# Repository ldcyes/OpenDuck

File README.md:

# OpenDuck 工程

**简体中文** | [English](README_EN.md)

本仓库整理 Microduck 的结构、电气、步态数值验证，以及 RK3576 驱动和训练适配源。**当前是工程仿真预发布，尚未通过实物制造与正常步速行走验收。**

**本次更新：[R29 干涉、线束与质量重算](hardware/r29-resolution/README.md) · [完整 Blender 与证据下载](https://github.com/ldcyes/OpenDuck/releases/tag/r29-r26-closure-candidate-20260929)。**

R29 将嘴部软件行程收至 0–10° 并修正下头壳；指定腿罩/电机配对在四条新质量慢速轨迹中的最低保守名义间隙下界为 11.407 mm。31 根线的防磨件和四工况动力学已补充，但嘴部闭合扭矩仍超过现行 0.05 Nm 结构限制，连续线束及制造公差尚无实物证明，**不能放行行走**。

沿用R25：31根头部导线改为底部接入，保留前盖与原外形比例；收拢活动线束并取消原侧面专用线孔。[底部走线特写](hardware/r25-bottom-head-entry/images/03-bottom-head-entry.png)。仍为工程候选，离散转头检查不代表连续运动或实物验收。

**历史四步回放：[R27：R26整机运动回放](hardware/r27-walk-replay/README.md)。** 使用已保存的195.44秒实际积分轨迹，逐帧驱动完整R26装配并复核覆盖件的刚体干涉增量；R26质量下的动力学和实物行走仍待验收。

**修复前干涉记录：[R28直接区间检查](hardware/r28-r26-interference/README.md)。** 两块新腿罩在四步轨迹的2,345组动态配对中没有新增穿透；最小保守间隙证明仅0.015 mm，制造公差未通过。旧头壳与嘴部在张嘴约8.75°后仍有真实相交。

**2026-09-24设计复核：[腿部比例与电机筛选](docs/proportion-study-20260924/README.md)。前期比较三种方案，现已采用A修改覆盖件；电机和腿长不变，实物步态未验收。**

[R24摄像头前盖](hardware/r24-head-front/README.md)与历史发布继续保留。

[R23合板支架、线束与热连接](hardware/r23-design/README.md)及其[完整工程](https://github.com/ldcyes/OpenDuck/releases/tag/r23-integrated-power-design-20260922)继续保留。

| 范围 | 早期基线（R23补充见上方入口） | 已有结果与边界 |
|---|---|---|
| 结构与装配 | R20 / R13.7 | 557件，名义质量4.195094 kg；72对参考窄/未证、34对实际名义接口仍保留 |
| 运动 | R21 / R13.8 | 实际身体侧倾与上头壳固定点横摆均减少约28.6%；慢速四步195.44 s；四种数值工况通过，原40%/30%目标未达到 |
| 电气 | R13原生板图 | 12种、13块；原规则DRC为0；额外启用忽略规则仍有43项警告；6块PCB、U2D2及相机待详细安装 |
| 驱动、交互和训练适配 | 已交付R8软件 | 有源码与历史测试；没有RK3576实机运行、GPU训练、实测BAM和批准权重；未完成R20/R21重新适配验收 |

## 从这里开始

- [直接下载完整装配、原始交付包和视频](https://github.com/ldcyes/OpenDuck/releases/tag/r13.8-simulation-20260913)：模型可独立打开；全部大文件保留原始内容，仅采用方便下载的英文文件名。
- [12种KiCad板、原理图及BOM入口](docs/pcb/原生电气设计入口.md)：每板均含项目文件、本地符号库与封装库。
- [PCB功能与主要器件](docs/pcb/01_全部PCB功能与主要器件.md)、[DRC和尺寸结论](docs/pcb/00_PCB检查与缩板结论.md)、[43项警告复核](docs/pcb/02_43项警告逐对象复核.md)。
- [结构修订和完整装配说明](docs/structure-r20/00_修复结果与查看说明.md)、[减摆结果](docs/motion-r21/00_减摆结果与查看说明.md)、[模型与视频查看方法](docs/motion-r21/02_模型与视频查看说明.md)。
- [软件、部署和训练真实入口](docs/software.md)、[复算与来源校验](docs/reproduction.md)、[来源和许可](NOTICE.md)。

## 下载内容

| 文件 | 内容 | 大小（十进制MB） |
|---|---|---:|
| [R13.7结构包](https://github.com/ldcyes/OpenDuck/releases/download/r13.8-simulation-20260913/R13.7-structure-gait.zip) | 结构、图纸、装配模型、沿用源快照和验证结果 | 730.83 |
| [R13.8步态更新包](https://github.com/ldcyes/OpenDuck/releases/download/r13.8-simulation-20260913/R13.8-reduced-sway.zip) | 新步态、四工况结果、减摆对照、更新代码与原始索引 | 603.51 |
| [PCB完整检查包](https://github.com/ldcyes/OpenDuck/releases/download/r13.8-simulation-20260913/PCB-R13-review.zip) | 12种原生板图、BOM、本地库与检查证据 | 1.99 |
| [完整Blender装配](https://github.com/ldcyes/OpenDuck/releases/download/r13.8-simulation-20260913/Microduck-R21-actual-comparison.blend) | 内含全部零件和实际运动，可直接打开 | 66.22 |
| [实际四步视频](https://github.com/ldcyes/OpenDuck/releases/download/r13.8-simulation-20260913/R21-four-steps-24x.mp4) | 约24倍播放速度；原始物理时间195.44 s | 1.14 |
| [同阶段对照视频](https://github.com/ldcyes/OpenDuck/releases/download/r13.8-simulation-20260913/R20-R21-phase-comparison.mp4) | 对齐参考阶段的R20/R21可视化 | 1.45 |

大小和SHA256见 [release-assets.json](release-assets.json) 与 [SHA256SUMS.txt](SHA256SUMS.txt)。GitHub自动生成的“Source code”压缩包只包含本仓库，不包含上述大型交付包。

## 仓库布局

| 目录 | 用途 |
|---|---|
| [hardware/kicad](hardware/kicad) | R13原生板图及本地库，201个文件保留原字节 |
| [docs](docs) | 适合GitHub浏览的说明、图和PCB复核 |
| [software/r8](software/r8) | 已交付R8驱动、交互、训练适配、相机/VLA源码与原验证记录 |
| [reference/work](reference/work) | R20/R21精选原始脚本、核心结果和两版实际轨迹；完整依赖在Release |
| [provenance](provenance) | 原始来源索引、复制哈希和文档路径转换记录 |
| [tools](tools) | 便携的仓库/附件校验和减摆复算入口 |
| [licenses](licenses) | 按来源分别保留的许可及上游说明 |

## 当前限制

正式四步从已经检查的新准备站姿开始；站姿过渡候选没有同等级完整验证。没有完成正常步速、温升、低电量持续扭矩或实物验收，也没有据此放行所有装配间隙。待安装件已有估算质量，实际安装时须替换，不能重复计重。

R8运行时的嘴部限位已按R29改为10°，旧标定/命令绑定会失效；其余硬件、策略及标定仍须重新核准。代码、模拟输入测试和61→14策略接口均不能替代新机械结构的实测标定或批准策略。软件入口默认使用未批准模板或dry-run，当前资料不构成上机运动许可。

项目派生自 Pollen Robotics 的 Microduck。软件、模型、KiCad库和Linux参考源码的许可分别见 [NOTICE.md](NOTICE.md)；本仓库没有给不明第三方资料统一增加商业许可。

## R22 紧凑电源候选（独立预发布）

[R22工程入口](hardware/r22-candidate/README.md)提供新的52×42 mm入口板、舵机电源与回生阶梯合板、原生KiCad/原理图/本地库、Gerber/钻孔和实际安装CAD。本次三个旧板改为两个候选板，总板面积减少14.01%；两块候选的冻结ERC/DRC及额外检查为0。原R13十二种板与R20/R21基线资料继续保留。

新增几何对原R21轨迹关节范围的93,595个动态配对满足≥2.2 mm的保守间隙证据；完整模型为733项装态几何/包络，并非733件制造BOM。这是几何复核，尚未按R22质量重新求解步态，也没有样机制造、温升、回生或行走验收。这些连接在R22交付时未闭合；后续工程设计见[R23入口](hardware/r23-design/README.md)，其物理验收边界另列。

- [R22独立预发布](https://github.com/ldcyes/OpenDuck/releases/tag/r22-compact-power-candidate-20260914)：[完整工程ZIP](https://github.com/ldcyes/OpenDuck/releases/download/r22-compact-power-candidate-20260914/R22-engineering-candidate.zip)、[可独立打开的静态Blender装配](https://github.com/ldcyes/OpenDuck/releases/download/r22-compact-power-candidate-20260914/Microduck-R22-static-candidate.blend)、[两板制造与检查包](https://github.com/ldcyes/OpenDuck/releases/download/r22-compact-power-candidate-20260914/R22-PCB-review.zip)、[SHA256](https://github.com/ldcyes/OpenDuck/releases/download/r22-compact-power-candidate-20260914/SHA256SUMS.txt)。
- [入口板安装](hardware/r22-candidate/mechanics/entry_mount/README.md)、[电容托架最终组合](hardware/r22-candidate/mechanics/motion_delta/CAP_FINAL_SUPPLEMENT.md)、[制造与验收边界](hardware/r22-candidate/fabrication/README.md)。
- [原始来源映射](provenance/r22-source-mapping.json)、[文档路径转换](provenance/r22-document-path-conversions.json)、[Git副本校验](provenance/r22-publication-file-check.json)、[附件摘要](provenance/r22-release-assets.json)。GitHub自动生成的Source code包不含完整工程ZIP和Blender。

R22没有更新RK3576驱动接口、保护阈值或批准训练权重；软件仍以既有R8真实入口及其未验收范围为准。来源和分别适用的许可继续见[NOTICE](NOTICE.md)。

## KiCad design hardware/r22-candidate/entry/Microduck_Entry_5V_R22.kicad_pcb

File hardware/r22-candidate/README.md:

# R22 紧凑电源设计候选

已完成两块实际四层PCB、原理图与本地库、BOM、接口、加工图及配套安装CAD。它们是用于工程审查的R22候选；现行R20结构/R21步态基线保留。没有样机，尚未完成制造、温升、动态回生、低电量及实物行走验收。

| 项目 | 原设计 | R22实际设计 | 面积变化 |
|---|---|---|---:|
| 5V入口板 | 65×45 mm，2925 mm² | 52×42 mm，2184 mm² | −25.33% |
| 舵机电源与回生 | 65×60加32×30 mm，4860 mm² | 阶梯合板，4510 mm²；最大外接65×75 mm | −7.20% |
| 本次三个旧板合计 | 7785 mm² | 两板6694 mm² | −14.01% |

若整机采用此候选，板型由12种减为11种，实际板数由13块减为12块（LEG5仍有左右两块）。这不是整机占用空间或续航同比改善；合板最大75 mm长度必须按阶梯轮廓检查。

## 打开工程与图纸

- [5V入口板说明](entry/README_R22_Entry.md)：打开 `entry/Microduck_Entry_5V_R22.kicad_pro`。58个封装，原159个原理图针与200个数字焊盘实例映射保持；五个SH同系列插头改顶插，保留原线端插壳及线序。
- [舵机电源＋回生说明](power_regen/README.md)：打开 `power_regen/Microduck_Power_Regen_R22.kicad_pro`。84个封装、292个焊盘，三页原理图；只合并SERVO_BUS/GND，其他控制与辅助电源网保持分离。J1改BM08顶插。
- [入口板安装图与STEP](mechanics/entry_mount/README.md)、[回生电容托架最终装配说明](mechanics/motion_delta/CAP_FINAL_SUPPLEMENT.md)。电容保留EEUFR1C222（2200µF/16V），改卧装并独立支承，须先在机外完成成形、固定与焊接。
- `fabrication/entry/`、`fabrication/power_regen/`：从已独立验证的原生副本导出的四层Gerber、正背阻焊/钢网、轮廓与分开的PTH/NPTH钻孔。按[制造与验收边界](fabrication/README.md)审查，不能把文件已生成等同于制造放行。
- 完整Blender和工程ZIP见[OpenDuck的R22预发布](https://github.com/ldcyes/OpenDuck/releases/tag/r22-compact-power-candidate-20260914)。KiCad、本次实际STEP/STL与Blender可分别打开；历史全过程复算仍依赖原R20/R21源快照及其运行库。

## 电气检查与计算的含义

根任务对冻结副本重新执行ERC、铺铜DRC、未连接检查、原理图/PCB一致性检查，并开启原来被忽略的DRC类别，两板结果均为0。独立复核另在副本开启四类默认忽略ERC检查，结果同样为0，见`final_review/supplemental_erc/`。这不等于实机电源合格。证据在 `final_verification/freeze_v1/entry/` 与 `final_verification/freeze_v2/power_regen/`；其他板仍沿用原R13审查结果。

两板均为1.60 mm、70/35/35/70 µm铜的四层结构。线宽≥0.20 mm，铺铜间距≥0.20 mm；入口板4对、合板15对局部逃线间距为0.175 mm，逐项记录。不能把“DRC为0”改写成全板任何间距均≥0.20 mm。孔铜厚度、塞孔填孔/盖铜、叠层与细间距均须由加工厂确认，见两板制造报告。

入口板用实际保存的铜区、走线、焊盘和贯穿孔建立直流电阻网格；含地回流的MOBILE与BENCH路径估计分别较原板降低50.67%与47.01%。这是数值铜路估算，源端/负载端焊点、线束、接头和动态纹波另计。保守设计预算下2.7 A板端约4.835 V仍未扣纹波与外部线损，不是整机满载验收值。

合板所选回生板内铜回路约4.866 mΩ@20°C；条件12.121 A时约59 mV、0.715 W。原两板纯板内铜约3.043 mΩ但不含删除的板间正负线对与接点，不能单凭合板宣称总回路降阻。12个换层孔的最大估计分流约9.9%，孔铜25 µm仍是假定。实际钳位上界、MOS开关损耗、回生脉冲和散热必须测试；RH050标称50 W不能直接当作机器人内可连续耗散50 W。

## 结构、模型与质量

Blender含三个场景：完整装配、入口板安装细节、合板/卧装电容/托架细节。733项表示468项原R20保留几何加265项新装态几何/包络，不是733个采购或制造件；另有9项拔插服务包络。各物体可以单独选取、隐藏，并查看原文件及所属关节。短线束预算不代表整机完整布线，保守器件包络不用于按体积计算器件重量。

入口板保留原底脚位置，改四孔框架与5 mm PEEK隔柱；背面元件2.7 mm高，对框架有名义2.3 mm余隙。四个M2工具通道用1.5 mm内六角L形扳手的Ø2×30 mm工作段核验。电容托架使用原H1/H2、不增加PCB孔，正X泄压端开放。套管上端已从z8.1改至7.9 mm；[精确STEP子集及间隙证据](mechanics/insulation_v2/subset_proof.json)确认两处原参考模型微交叠消除，套管到弯脚工程包络的最小名义距离约0.025 mm。这处很小的名义间隙仍需实物成形/绝缘验收。

安装、静态接触及按R21原轨迹关节范围的几何增量证据见 `mechanics/motion_delta/` 的最终报告。该检查可评价新几何在既定关节范围内的分离，不产生新的动力学仿真或质量/重心结论。

[有限质量与重心审查](integration/mass_review/质量与重心影响_有限范围审查.md)显示：增加内层铜后，五块新旧裸板材模型的铜名义增加约2.741 g；裸材减少约0.937 g，加本次附件毛差后名义约+0.04 g，误差足以改变符号。器件、焊料、换插头及完整线束未称量，不能给出精确新整机质量或COM，也不能继承R21动态平衡、扭矩或行走放行。

## 仍需闭合的实际工程项目

1. 合板到机身的主支架、完整电阻/电源线束、热连接与装入顺序。电容托架只固定电容到PCB，不能视为完成PCB到机身的主支承。
2. 加工厂叠层、孔铜、填孔盖铜、局部细间距及装配工艺；卧装电容成形和绝缘、绑带拉脱与热蠕变、M2叠层拧紧试样。
3. 5V全负载/低输入/纹波/切换、电源温升、回生瞬态与功率电阻温度；最终质量替换后重新核对重心和运动，再进行实体受载与行走验收。

本次不改变RK3576软件接口、保护阈值或历史训练权重。来源与分别适用的许可沿用[仓库NOTICE](https://github.com/ldcyes/OpenDuck/blob/main/NOTICE.md)；历史原生设计和交付包未覆盖。

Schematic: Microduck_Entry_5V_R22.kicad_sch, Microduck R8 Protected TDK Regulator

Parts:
C1, C2, C3, C4, C5, C6, C7, C17: 100nF; C_0603_1608Metric; MPN GRM188R71H104KA93D
C8: 100pF C0G; C_0603_1608Metric; MPN GRM1885C1H101JA01D
C9, C10: 10uF 50V X7R; C_1210_3225Metric; MPN GRM32ER71H106KA12L
C11: 100uF 35V; CP_Radial_D8.0mm_P3.50mm; MPN EEUFR1V101
C12, C13, C14, C15: 22uF 25V X7R; C_1210_3225Metric; MPN GRM32ER71E226KE15L
C16: 10uF 10V; C_0805_2012Metric; MPN GRM21BR71A106KE51L
C18: 270uF 10V; CP_Radial_D6.3mm_P2.50mm; MPN EEUFR1A271
F1: 2A 125V LOGIC INPUT; Fuse_Littelfuse_448; MPN 0448002.MR
H1, H2, H3, H4: M2 NPTH; MountingHole_2.2mm_M2; MPN NO PART
J1: NTC BAT 10k 3977K; JST_SH_SM02B-SRSS-TB_1x02-1MP_P1.00mm_Horizontal; MPN SM02B-SRSS-TB(LF)(SN)
J2: NTC TDK 10k 3977K; JST_SH_SM02B-SRSS-TB_1x02-1MP_P1.00mm_Horizontal; MPN SM02B-SRSS-TB(LF)(SN)
J3: NTC BRAKE 10k 3977K; JST_SH_BM02B-SRSS-TB_1x02-1MP_P1.00mm_Vertical; MPN BM02B-SRSS-TB(LF)(SN)
J4: TO CM4 LOGIC CTRL; JST_SH_SM10B-SRSS-TB_1x10-1MP_P1.00mm_Horizontal; MPN SM10B-SRSS-TB(LF)(SN)
J5: TO TDK POWER CTRL; JST_SH_BM08B-SRSS-TB_1x08-1MP_P1.00mm_Vertical; MPN BM08B-SRSS-TB(LF)(SN)
J6, J7: TMP302 THERMAL STOP; JST_SH_BM03B-SRSS-TB_1x03-1MP_P1.00mm_Vertical; MPN BM03B-SRSS-TB(LF)(SN)
J8: BRAKE INA226 0x42 TELEMETRY; JST_SH_BM05B-SRSS-TB_1x05-1MP_P1.00mm_Vertical; MPN BM05B-SRSS-TB(LF)(SN)
R1, R2: 10R 0.1%; R_0603_1608Metric; MPN RT0603BRD0710RL
R3, R4, R5, R14: 10k 0.1%; R_0603_1608Metric; MPN RT0603BRD0710KL
R6, R7, R8, R9: 1k; R_0603_1608Metric; MPN ERJ-3EKF1001V
R10: 41.0k 0.1%; R_0603_1608Metric; MPN RT0603BRD0741KL
R11: 10.0k 0.1%; R_0603_1608Metric; MPN RT0603BRD0710KL
R12: 88.7k 0.1%; R_0603_1608Metric; MPN RT0603BRD0788K7L
R13: 32.4k 0.1%; R_0603_1608Metric; MPN RT0603BRD0732K4L
RS1: 2mOhm 1% 3W KELVIN; WSL2726_Kelvin; MPN WSL27262L000FEA
U1: BATTERY INA226 0x40; TI_DGS0010A_Manufacturer_1p45x0p30; MPN INA226AIDGSR
U2: NTC AND EXCITATION 0x48; TI_DGS0010A_Manufacturer_1p45x0p30; MPN ADS1115IDGSR
U3: 4S to 5.10V 3A MODULE; LMZM33603_RLR; MPN LMZM33603RLRR
U4: BENCH PRIORITY REVERSE BLOCK; TPS2117_DRL; MPN TPS2117DRLR
W1: BAT_FUSED; WirePad_2p4mm_6mm; MPN SOLDER AWG16
W2, W4: GND; WirePad_2p4mm_6mm; MPN SOLDER AWG16
W3: BAT_MON; WirePad_2p4mm_6mm; MPN SOLDER AWG16
W5: BENCH_5V; WirePad_2p4mm_6mm; MPN SOLDER AWG20
W6, W8: GND; WirePad_2p4mm_6mm; MPN SOLDER AWG20
W7: SYSTEM_5V; WirePad_2p4mm_6mm; MPN SOLDER AWG20

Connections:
+3V3: C2.1, C7.1, J4.2 (PIN2), J5.2 (PIN2), J6.2 (PIN2), J7.2 (PIN2), J8.2 (PIN2), R3.1, R4.1, R5.1, R9.1, U1.6 (VS), U2.8 (VDD)
ADC_BAT: C3.1, R6.2, U2.4 (AIN0)
ADC_BRAKE: C5.1, R8.2, U2.6 (AIN2)
ADC_EXC: C6.1, R9.2, U2.7 (AIN3)
ADC_TDK: C4.1, R7.2, U2.5 (AIN1)
AGND_5V: R11.2, R12.2, U3.1 (AGND_INTERNAL)
BAT_FUSED: RS1.1 (I+), W1.1
BAT_MON: F1.1, RS1.4 (I-), U1.8 (VBUS), W3.1
BAT_SENSE_N: R2.1, RS1.3 (S-)
BAT_SENSE_P: R1.1, RS1.2 (S+)
BENCH_5V: C16.1, R13.1, U4.3 (VIN1), U4.5 (MODE), W5.1
BENCH_VALID: R13.2, R14.1, U4.4 (PR1)
BRAKE_ACTIVE_N: J4.8 (PIN8), J8.5 (PIN5)
FB_5V: C8.2, R10.2, R11.1, U3.16 (FB)
GND: C2.2, C3.2, C4.2, C5.2, C6.2, C7.2, C9.2, C10.2, C11.2, C12.2, C13.2, C14.2, C15.2, C16.2, C17.2, C18.2, J1.2 (PIN2), J2.2 (PIN2), J3.2 (PIN2), J4.1 (PIN1), J4.9 (PIN9), J4.10 (PIN10), J5.1 (PIN1), J5.8 (PIN8), J6.1 (PIN1), J7.1 (PIN1), J8.1 (PIN1), R14.2, U1.1 (A1), U1.2 (A0), U1.7 (GND), U2.1 (ADDR), U2.3 (GND), U3.5 (PGND), U3.14 (PGND), U3.15 (PGND), U3.18 (EP_PGND), U4.1 (GND), W2.1, W4.1, W6.1, W8.1
I2C_SCL: J4.4 (PIN4), J5.4 (PIN4), J8.4 (PIN4), U1.5 (SCL), U2.10 (SCL)
I2C_SDA: J4.3 (PIN3), J5.3 (PIN3), J8.3 (PIN3), U1.4 (SDA), U2.9 (SDA)
INA_N: C1.2, R2.2, U1.9 (IN-)
INA_P: C1.1, R1.2, U1.10 (IN+)
LOGIC_VIN: C9.1, C10.1, C11.1, F1.2, U3.2 (EN), U3.4 (VIN)
MOBILE_5V: C8.1, C12.1, C13.1, C14.1, C15.1, R10.1, U3.6 (VOUT), U3.7 (VOUT), U3.8 (EP_VOUT), U4.6 (VIN2)
NTC_BAT: J1.1 (PIN1), R3.2, R6.1
NTC_BRAKE: J3.1 (PIN1), R5.2, R8.1
NTC_TDK: J2.1 (PIN1), R4.2, R7.1
RT_5V: R12.1, U3.3 (RT)
RUN_OK: J4.6 (PIN6), J5.6 (PIN6), J6.3 (PIN3), J7.3 (PIN3)
RUN_REQ: J4.5 (PIN5), J5.5 (PIN5)
SW_INTERNAL: U3.9 (SW), U3.10 (SW), U3.11 (SW)
SYSTEM_5V: C17.1, C18.1, U4.2 (VOUT), U4.7 (VOUT), W7.1
TDK_IMON: J4.7 (PIN7), J5.7 (PIN7)

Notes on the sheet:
R8 CONTROLLED PROTOTYPE / 4S -> 10.8V / ACTIVE CURRENT LATCH + REVERSE BLOCK / SOURCE DATASHEETS REQUIRED
J1.5 RUN_REQ defaults LOW. OC latches via INA300; clear only while RUN_REQ LOW. Brake board mandatory on SERVO_BUS.
TDK ITRIM tolerance is TYPICAL; INA300 provides independent trip. 10A copper target requires physical thermal qualification.

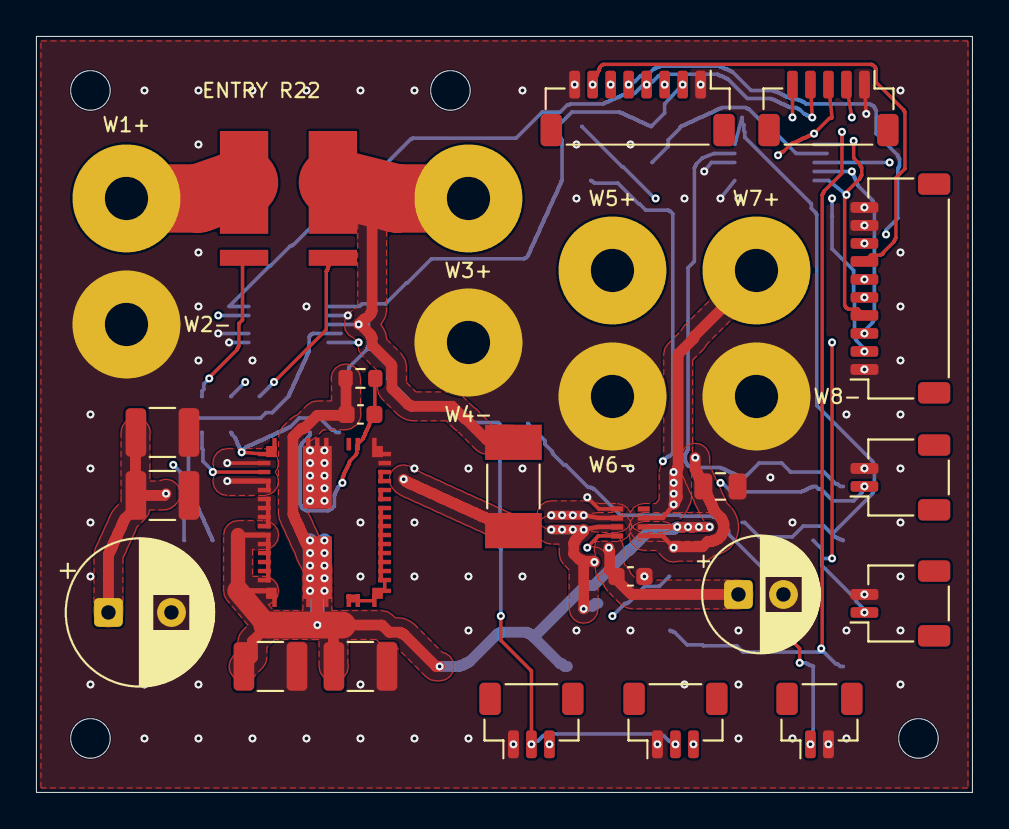
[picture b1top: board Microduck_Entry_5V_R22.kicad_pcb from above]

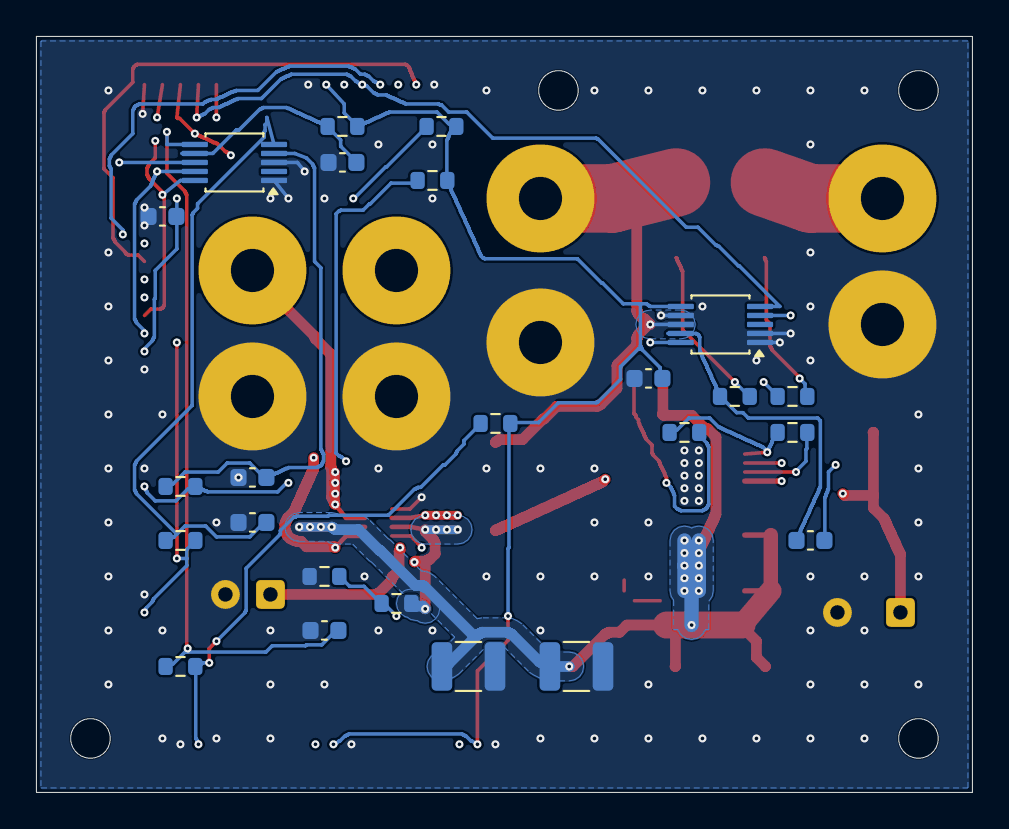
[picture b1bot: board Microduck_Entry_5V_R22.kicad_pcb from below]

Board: 4 copper layers, 52.0 x 42.0 mm, 58 parts (24 on the bottom side), 30 nets.

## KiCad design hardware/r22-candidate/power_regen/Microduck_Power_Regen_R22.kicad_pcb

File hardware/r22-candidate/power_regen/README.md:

# R22 TDK Power + Regen 合板

已完成可编辑原理图、真实四层 PCB 和本地库。阶梯板面积 4510 mm²，比原 65×60 + 32×30 mm 两板总面积 4860 mm² 少 350 mm²（7.20%）。原 TDK 模块本体、四个安装孔和原 TDK 器件位置保留，回生电容采用原料号卧装，J1 因实际拔插通道冲突改为同系列 BM08 顶插。当前为工程候选，未制造，未完成热、回生瞬态、低电量或行走验收。

打开 `Microduck_Power_Regen_R22.kicad_pro`；根原理图包含 `power.kicad_sch` 与 `regen.kicad_sch`。`fp-lib-table`、`sym-lib-table` 和本地 `footprints/`、符号库随项目交付，不依赖源目录可写。原生 PCB 是本次权威结果；中间生成/路由脚本仅保留过程追踪，不能只运行早期 `build.py` 覆盖最终板。

| 内容 | 文件 |
|---|---|
| 三页可编辑原理图及浏览版 | `Microduck_Power_Regen_R22.kicad_sch`、`Schematic_R22.pdf`、`schematic_svg/` |
| 实际板图及叠层 | `Microduck_Power_Regen_R22.kicad_pcb`、同名 `.kicad_pro` / `.kicad_dru` |
| 四层铜 PDF / 前背 SVG | `PCB_Copper_R22.pdf`、`PCB_Front.svg`、`PCB_Back.svg` |
| 正背装配图 | `Assembly_Front.svg`、`Assembly_Back.svg`、相应 PNG |
| BOM、源针网及删改映射 | `BOM_R22.csv`、`Pin_to_Net_R22.csv`、`merge_mapping.json`、`equivalence_audit.json` |
| 安装/焊线/插头/孔位接口 | `Board_Interface_R22_Power_Regen.json` |
| 制造、保护、承流和验收边界 | `Validation_Report.md`、`Fabrication_Local_Clearances.json`、`Current_Thermal_Screen.json`、`DC_Copper_Regen_Loop_Final.json` |
| 验证 | `drc.json`、`erc.json`、`verification/enabled/`、`final_sha256.json` |

只在 SERVO_BUS 和 GND 上合网。保留两域 +3V3、回生 5V、内部 SHUNT / INA / 控制网络的独立性；不能据同名直接合并。主电源 INA226 地址 0x41、回生 INA226 地址 0x42、LM74800、INA300、比较器迟滞、驱动和默认关闭保持源功能。唯一 MPN 替代是有安装实形证据的 J1：SM08B → BM08B，SHR-08V-S / SSH-003T-P0.2-H 及八针网络不变。所有其他 MPN 和值均与现行 R13 两源板逐项核对。

铜图前后层统一使用原生 XY 俯视坐标便于对照；`Assembly_Back.svg`/PNG 为翻到背面后的镜像装配视图。装配精确编号、坐标和方向以 BOM 与针网表为准。

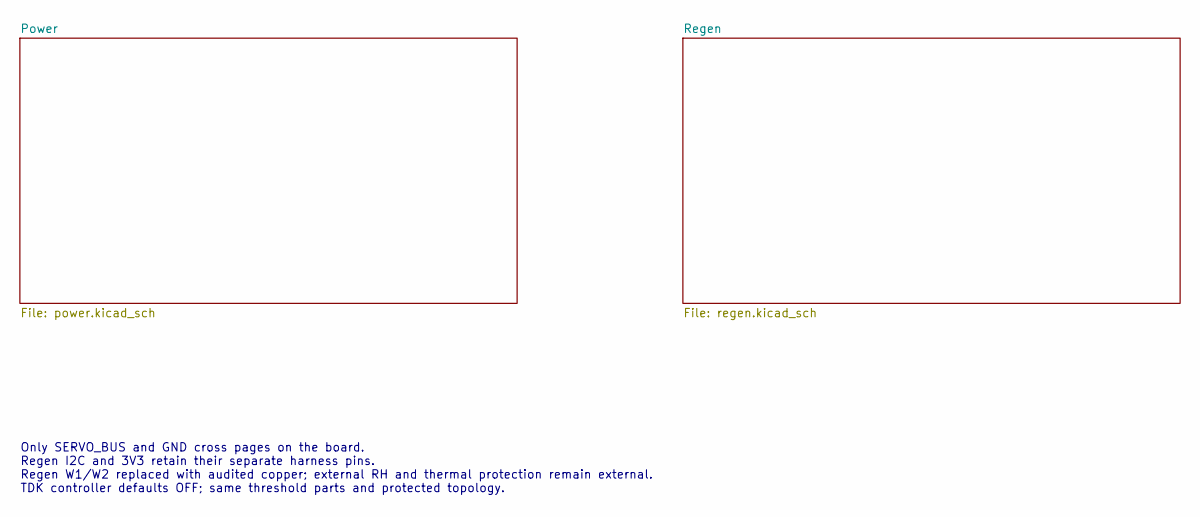
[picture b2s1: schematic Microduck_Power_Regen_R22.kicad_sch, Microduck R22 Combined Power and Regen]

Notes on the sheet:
Only SERVO_BUS and GND cross pages on the board. Regen I2C and 3V3 retain their separate harness pins. Regen W1/W2 replaced with audited copper; external RH and thermal protection remain external. TDK controller defaults OFF; same threshold parts and protected topology.

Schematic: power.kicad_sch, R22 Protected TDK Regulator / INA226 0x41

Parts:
C1, C2, C3: 680uF 25V 20%; CP_Radial_D10.0mm_P5.00mm; MPN EEUFR1E681
C4, C5, C6, C7, C8, C9, C10, C11, C12, C15: 100nF; C_0603_1608Metric; MPN GRM188R71H104KA93D
C13, C14, C16, C17, C18, C19: 10uF 50V; C_1210_3225Metric; MPN GRM32ER71H106KA12L
H1, H2, H3, H4: M2 NPTH; MountingHole_2.2mm_M2; MPN NO PART
J1: CONTROL 3.3V / RUN DEFAULT OFF; JST_SH_BM08B-SRSS-TB_1x08-1MP_P1.00mm_Vertical; MPN BM08B-SRSS-TB(LF)(SN)
Q1, Q2: 60V 2.2mOhm @10V; CSD18540Q5B_DNK; MPN CSD18540Q5B
Q3: TDK enable sink; SOT-23; MPN BSS138
R1: 2.45k 0.1%; R_0603_1608Metric; MPN RT0603BRD072K45L
R2: 17.4k 0.1%; R_0603_1608Metric; MPN RT0603BRD0717K4L
R3: 1k; R_0603_1608Metric; MPN ERJ-3EKF1001V
R4: 8.38k 0.1%; R_0603_1608Metric; MPN RT0603BRD078K38L
R5: 1k 0.1%; R_0603_1608Metric; MPN RT0603BRD071KL
R6: 1.2k; R_0603_1608Metric; MPN ERJ-3EKF1201V
R7, R8: 100k; R_0603_1608Metric; MPN ERJ-3EKF1003V
R9: 1.10k 0.1%; R_0603_1608Metric; MPN RT0603BRD071K1L
R10, R11: 10R 0.1%; R_0603_1608Metric; MPN RT0603BRD0710RL
RS1: 2mOhm 1% 3W KELVIN; WSL2726_Kelvin; MPN WSL27262L000FEA
U1: TDK i7C2W020A120V-P03-R; TDK_i7C_P03; MPN i7C2W020A120V-P03-R
U2: IDEAL DIODE + OV CUT; WSON-12-1EP_3x3mm_P0.5mm_EP1.5x2.5mm; MPN LM74800QDRRRQ1
U3: SERVO CURRENT / VBUS 0x41; TI_DGS0010A_1p45x0p30; MPN INA226AIDGSR
U4: HARDWARE OC LATCH; TI_DGS0010A_1p45x0p30; MPN INA300AIDGSR
W1: 4S SWITCHED +; WirePad_2p4mm_6mm; MPN SOLDER AWG16
W2: GND INPUT; WirePad_2p4mm_6mm; MPN SOLDER AWG16
W3: SERVO 10.8V; WirePad_2p4mm_6mm; MPN SOLDER AWG16
W4: GND OUTPUT; WirePad_2p4mm_6mm; MPN SOLDER AWG16

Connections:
+3V3: C10.1, C11.1, J1.2 (PIN2), U3.2 (A0), U3.6 (VS), U4.4 (ENABLE), U4.9 (VS)
BAT_SW: C1.1, C12.1, C13.1, C14.1, C16.1, C17.1, C18.1, C19.1, U1.1 (VIN), W1.1
CP_CAP: C5.1, U2.11 (CAP)
DGATE: Q1.4 (G), U2.1 (DGATE)
GND: C1.2, C2.2, C3.2, C4.2, C6.2, C7.2, C8.2, C10.2, C11.2, C12.2, C13.2, C14.2, C15.2, C16.2, C17.2, C18.2, C19.2, J1.1 (PIN1), J1.8 (PIN8), Q3.2 (S), R1.2, R2.2, R5.2, R7.2, R8.2, R9.2, U1.3 (GND), U1.4 (GND), U1.32 (SYNC), U2.7 (GND), U3.1 (A1), U3.7 (GND), U4.8 (GND), W2.1, W4.1; also elsewhere on the board
HGATE: Q2.4 (G), U2.8 (HGATE)
I2C_SCL: J1.4 (PIN4), U3.5 (SCL)
I2C_SDA: J1.3 (PIN3), U3.4 (SDA)
IMON_RAW: R3.1, U1.34 (IMON)
INA_N: C9.2, R11.2, U3.9 (IN-)
INA_P: C9.1, R10.2, U3.10 (IN+)
ITRIM: R2.1, U1.5 (ITRIM)
MID_DRAIN: C5.2, C6.1, Q1.5 (D), Q1.6 (D), Q1.7 (D), Q1.8 (D), Q2.5 (D), Q2.6 (D), Q2.7 (D), Q2.8 (D), R4.1, U2.3 (VSNS), U2.4 (SW), U2.10 (VS), U2.12 (C)
OC_LIMIT: R9.1, U4.3 (LIMIT)
OV_SENSE: R4.2, R5.1, U2.5 (OV)
PRE_SHUNT: C8.1, Q2.1 (S), Q2.2 (S), Q2.3 (S), RS1.1 (I+), U2.9 (OUT)
REG_RAW: C2.1, C3.1, C7.1, C15.1, Q1.1 (S), Q1.2 (S), Q1.3 (S), U1.7 (SENSE+), U1.8 (VOUT), U2.2 (A)
RUN_OK: J1.6 (PIN6), Q3.1 (G), R6.2, R7.1, U2.6 (EN/UVLO), U4.5 (ALERT)
RUN_REQ: J1.5 (PIN5), R6.1, R8.1, U4.6 (LATCH)
SENSE_N: R11.1, RS1.3 (S-), U4.2 (IN-)
SENSE_P: R10.1, RS1.2 (S+), U4.1 (IN+)
SERVO_BUS: RS1.4 (I-), U3.8 (VBUS), W3.1; also elsewhere on the board
TDK_IMON: C4.1, J1.7 (PIN7), R3.2
TDK_ON_N: Q3.3 (D), U1.2 (ON/OFF)
VTRIM: R1.1, U1.6 (TRIM)
